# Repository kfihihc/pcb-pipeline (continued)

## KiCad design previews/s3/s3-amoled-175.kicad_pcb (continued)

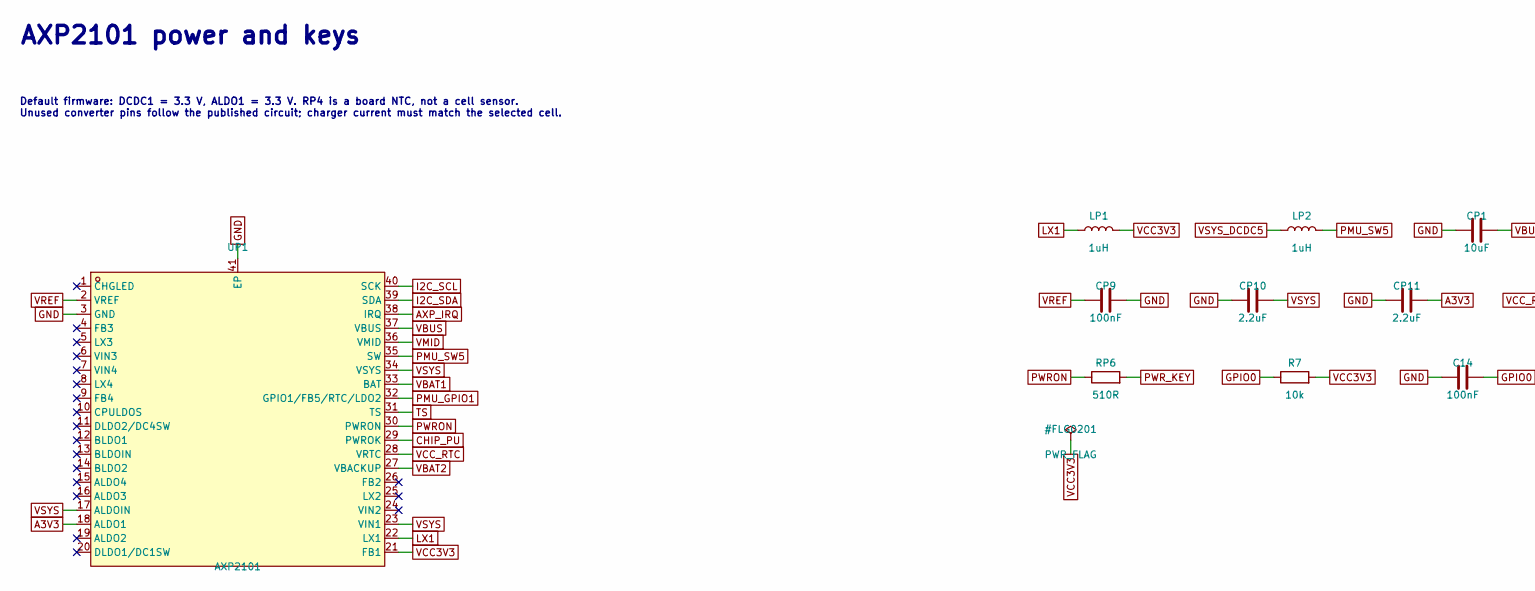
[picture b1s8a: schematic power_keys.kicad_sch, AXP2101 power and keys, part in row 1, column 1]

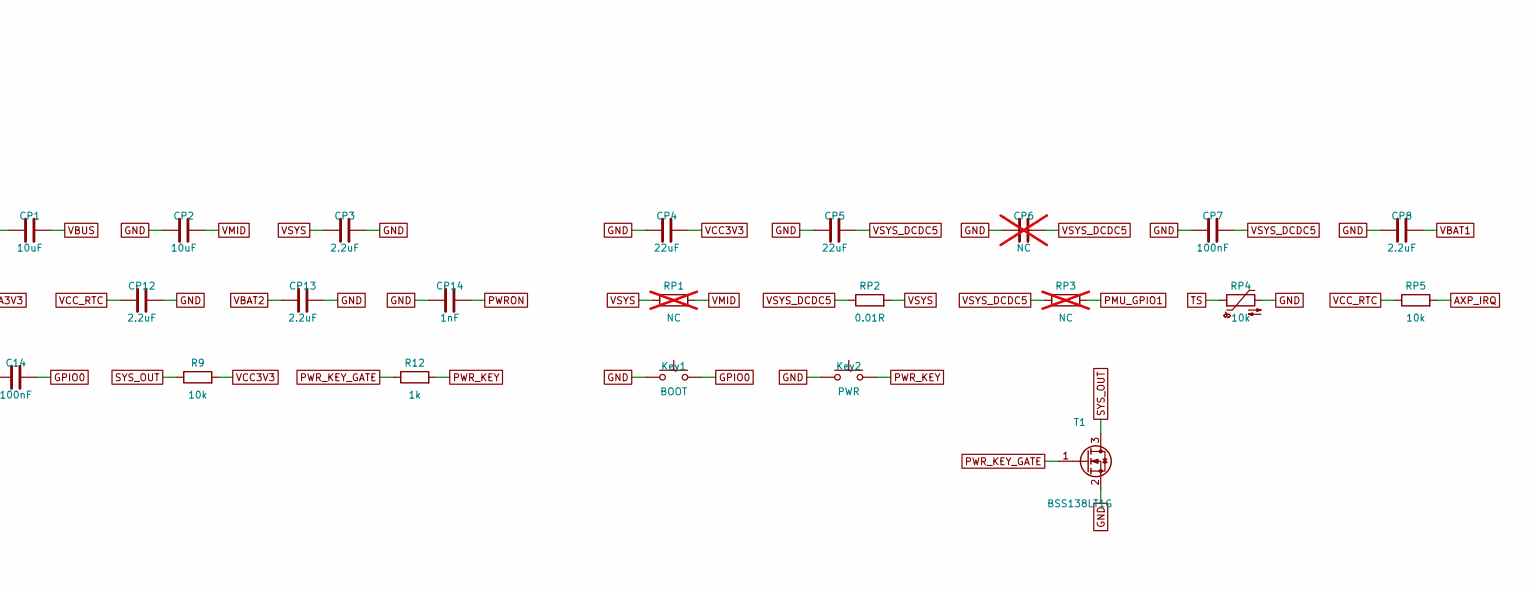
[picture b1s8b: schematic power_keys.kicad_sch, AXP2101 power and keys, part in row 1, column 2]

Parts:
C14: 100nF; C_0201_0603Metric_Tight; LCSC C190183
CP1, CP2: 10uF; C_0603_1608Metric_Tight; LCSC C92487
CP3, CP8, CP10, CP11, CP12, CP13: 2.2uF; C_0201_0603Metric_Tight; LCSC C386031
CP4, CP5: 22uF; C_0603_1608Metric_Tight; LCSC C86295
CP6: NC; C_0201_0603Metric_Tight; not fitted
CP7, CP9: 100nF; C_0201_0603Metric_Tight; LCSC C190183
CP14: 1nF; C_0201_0603Metric_Tight; LCSC C505464
Key1: BOOT; SW_EVPAE_Grounded; MPN EVPAEDB2A; LCSC C79150
Key2: PWR; SW_EVPAE_Grounded; MPN EVPAEDB2A; LCSC C79150
LP1, LP2: 1uH; L_1008_2520Metric_Tight; MPN WPN252012H1R0MT; LCSC C98348
R7, R9: 10k; R_0201_0603Metric_Tight; LCSC C473048
R12: 1k; R_0201_0603Metric_Tight; LCSC C138165
RP1: NC; R_0603_1608Metric_Tight; not fitted
RP2: 0.01R; R_0603_1608Metric_Tight; LCSC C728437
RP3: NC; R_0201_0603Metric_Tight; not fitted
RP4: 10k; R_0603_1608Metric_Tight; MPN NCP18XH103F03RB; LCSC C13564
RP5: 10k; R_0201_0603Metric_Tight; LCSC C473048
RP6: 510R; R_0201_0603Metric_Tight; LCSC C304550
T1: BSS138LT1G; SOT-23; MPN BSS138LT1G; LCSC C82045
UP1: AXP2101; QFN-40_L5.0-W5.0-P0.40-TL-EP3.4; MPN AXP2101; LCSC C3036461

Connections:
A3V3: CP11.2, UP1.18 (ALDO1); also elsewhere on the board
AXP_IRQ: RP5.2, UP1.38 (IRQ)
CHIP_PU: UP1.29 (PWROK); also elsewhere on the board
GND: C14.1, CP1.1, CP2.1, CP3.2, CP4.1, CP5.1, CP6.1, CP7.1, CP8.1, CP9.2, CP10.1, CP11.1, CP12.2, CP13.2, CP14.1, Key1.1, Key2.1, RP4.2, T1.2 (S), UP1.3 (GND), UP1.41 (EP); also elsewhere on the board
GPIO0: C14.2, Key1.2, R7.1; also elsewhere on the board
I2C_SCL: UP1.40 (SCK); also elsewhere on the board
I2C_SDA: UP1.39 (SDA); also elsewhere on the board
LX1: LP1.1, UP1.22 (LX1)
PMU_GPIO1: RP3.2, UP1.32 (GPIO1/FB5/RTC/LDO2)
PMU_SW5: LP2.2, UP1.35 (SW)
PWRON: CP14.2, RP6.1, UP1.30 (PWRON)
PWR_KEY: Key2.2, R12.2, RP6.2
PWR_KEY_GATE: R12.1, T1.1 (G)
SYS_OUT: R9.1, T1.3 (D); also elsewhere on the board
TS: RP4.1, UP1.31 (TS)
VBAT1: CP8.2, UP1.33 (BAT); also elsewhere on the board
VBAT2: CP13.1, UP1.27 (VBACKUP)
VBUS: CP1.2, UP1.37 (VBUS); also elsewhere on the board
VCC3V3: CP4.2, LP1.2, R7.2, R9.2, UP1.21 (FB1); also elsewhere on the board
VCC_RTC: CP12.1, RP5.1, UP1.28 (VRTC)
VMID: CP2.2, RP1.2, UP1.36 (VMID)
VREF: CP9.1, UP1.2 (VREF)
VSYS: CP3.1, CP10.2, RP1.1, RP2.2, UP1.17 (ALDOIN), UP1.23 (VIN1), UP1.34 (VSYS); also elsewhere on the board
VSYS_DCDC5: CP5.2, CP6.2, CP7.2, LP2.1, RP2.1, RP3.1

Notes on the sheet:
Default firmware: DCDC1 = 3.3 V, ALDO1 = 3.3 V. RP4 is a board NTC, not a cell sensor. Unused converter pins follow the published circuit; charger current must match the selected cell.
AXP2101 power and keys

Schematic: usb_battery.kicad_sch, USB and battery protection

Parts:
C108: 100nF; C_0201_0603Metric_Tight; LCSC C190183
H1: USB-C 16P; USB-C-SMD_SHOU_TYPE-C-16P-CB1.6; MPN TYPE-C 16P CB1.6 073; LCSC C2906290
J1: BAT 1.25mm 2P; CONN-SMD_P1.25-H_1.25T-2PWT; MPN 1.25T-2P SMD R/A; LCSC C22074
P1, P2: TP; TestPoint_Pad_D1.0mm_Tight
Q1: AO3400A; SOT-23; MPN AO3400A; LCSC C20917
Q2: AO3401A; SOT-23; MPN AO3401A; LCSC C15127
Q3: MMBT3904; SOT-23; MPN MMBT3904; LCSC C20526
R1, R2: 5.1k; R_0201_0603Metric_Tight; LCSC C473460
R13, R14: 22R; R_0201_0603Metric_Tight; LCSC C155743
R49: 1M; R_0201_0603Metric_Tight; LCSC C295786
R52: 22k; R_0201_0603Metric_Tight; LCSC C473469
R53: 100k; R_0201_0603Metric_Tight; LCSC C106230
TVS1: LTVS16H5.0ET5G; DFN1610-2L_LTVS16H5.0ET5G_Tight; MPN LTVS16H5.0ET5G; LCSC C383280
U9: USBLC6-2P6; SOT-666_Tight; MPN USBLC6-2P6; LCSC C2827693

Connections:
BAT_BASE: Q3.1 (B), R52.2, R53.1
BAT_DETECT: Q2.3 (D), R52.1
BAT_GATE: C108.2, Q1.1 (G), Q3.3 (C), R49.2
BAT_NEG: J1.2, Q1.3 (D), Q2.2 (S)
GND: H1.25 (EH), H1.26 (EH), H1.27 (EH), H1.28 (EH), H1.A1 (GND), H1.A12 (GND), H1.B1 (GND), H1.B12 (GND), J1.3, J1.4, Q1.2 (S), Q3.2 (E), R1.1, R2.1, R53.2, TVS1.2 (A), U9.2 (GND); also elsewhere on the board
USB_CC1: H1.A5 (CC1), R2.2
USB_CC2: H1.B5 (CC2), R1.2
USB_DN_MCU: R13.2; also elsewhere on the board
USB_DP_MCU: R14.2; also elsewhere on the board
USB_N: H1.A7 (DN1), H1.B7 (DN2), P1.1, R13.1, U9.1 (I/O1), U9.6 (I/O1)
USB_P: H1.A6 (DP1), H1.B6 (DP2), P2.1, R14.1, U9.3 (I/O2), U9.4 (I/O2)
VBAT1: C108.1, J1.1, Q2.1 (G), R49.1; also elsewhere on the board
VBUS: H1.A4 (VBUS), H1.A9 (VBUS), H1.B4 (VBUS), H1.B9 (VBUS), TVS1.1 (C), U9.5 (VBUS); also elsewhere on the board

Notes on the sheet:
USB ESD: place U9 at connector. Battery return BAT_NEG must remain isolated from GND. AN171 Fig.4 adapted for 1S; bench validation of hot-plug and charging remains required.
USB and battery protection

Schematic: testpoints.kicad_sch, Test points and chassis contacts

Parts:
H2, H4: MH_GND; MountingHole_1.6mm_PTH_Pad2.35
TP1, TP2, TP3, TP4, TP5, TP6, TP7, TP8, TP9, TP10, TP11, TP12, TP13, TP14, TP15, TP16, TP17, TP18, TP19, TP20, TP21: TP; TestPoint_Pad_D1.0mm_Tight

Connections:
CHIP_PU: TP11.1; also elsewhere on the board
ES7210_DMIC_CLK: TP20.1; also elsewhere on the board
ES7210_INT: TP12.1; also elsewhere on the board
GND: H2.1, H4.1, TP1.1, TP3.1, TP17.1, TP19.1, TP21.1; also elsewhere on the board
GPIO17: TP13.1; also elsewhere on the board
GPIO18: TP14.1; also elsewhere on the board
GPIO39: TP15.1; also elsewhere on the board
GPIO40: TP16.1; also elsewhere on the board
GPIO41: TP9.1; also elsewhere on the board
GPIO42: TP10.1; also elsewhere on the board
I2C_SCL: TP7.1; also elsewhere on the board
I2C_SDA: TP8.1; also elsewhere on the board
U0RXD: TP5.1; also elsewhere on the board
U0TXD: TP6.1; also elsewhere on the board
VBUS: TP2.1; also elsewhere on the board
VCC3V3: TP4.1, TP18.1; also elsewhere on the board

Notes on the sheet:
TP12 = ES7210 INT; TP20 = ES7210 DMIC_CLK. H2/H4: plated 1.6 mm holes, 2.35 mm pad, to GND (PDF edge distance + product photo ring); verify on a unit.
Test points and chassis contacts

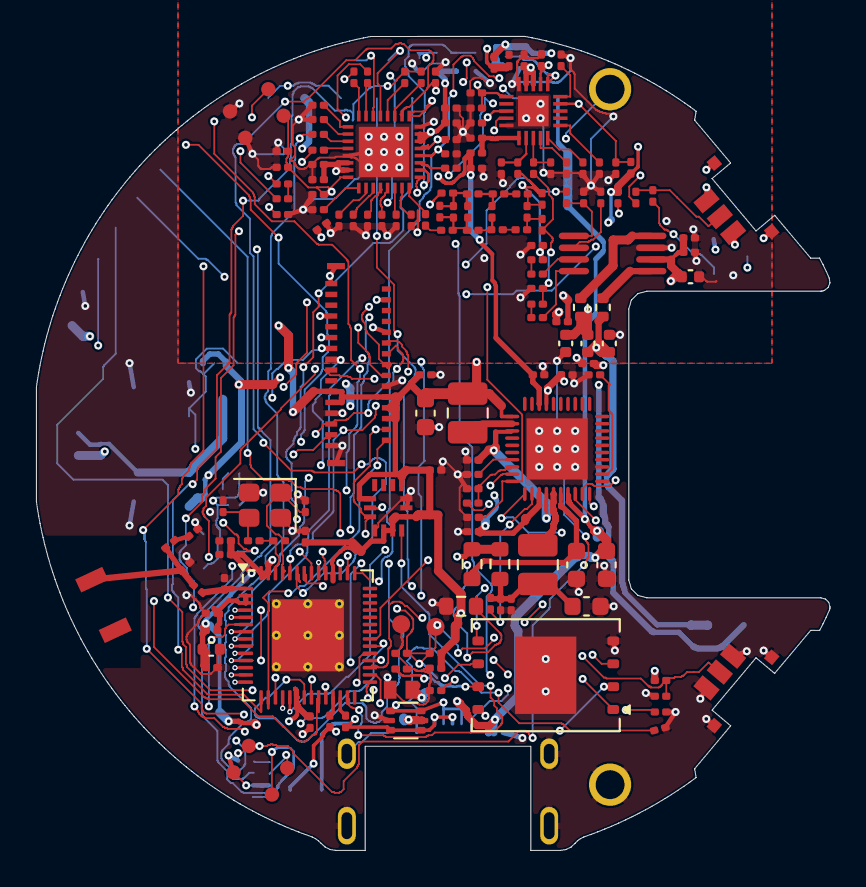
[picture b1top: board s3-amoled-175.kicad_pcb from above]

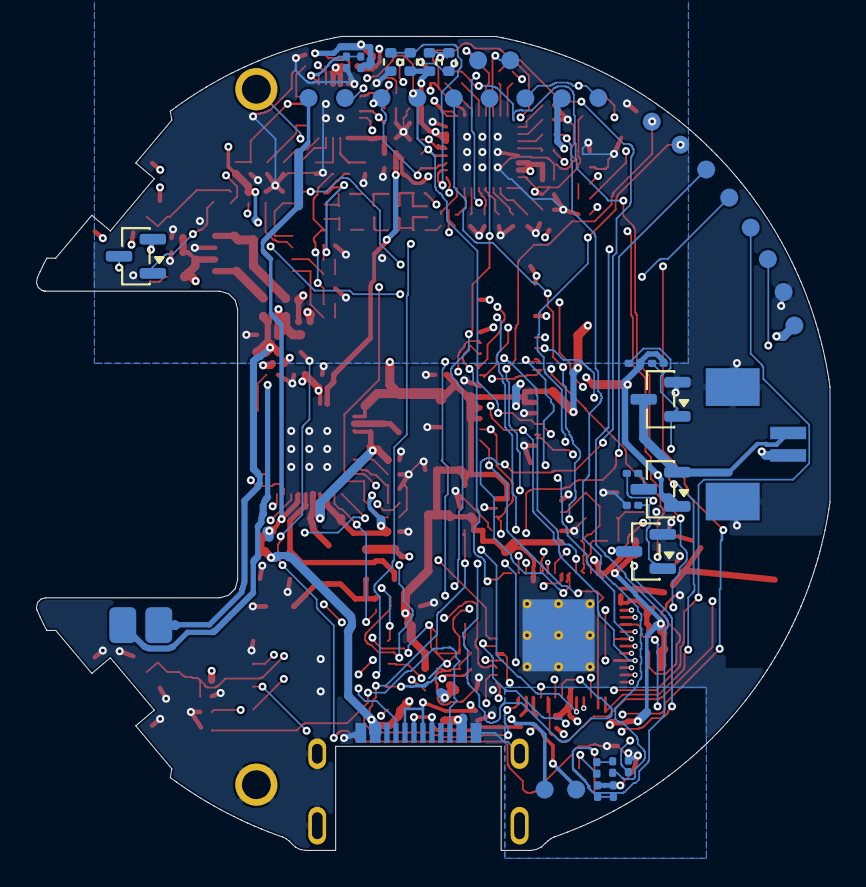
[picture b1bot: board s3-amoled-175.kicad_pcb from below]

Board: 4 copper layers, 44.1 x 45.2 mm, 202 parts (43 on the bottom side), 134 nets.

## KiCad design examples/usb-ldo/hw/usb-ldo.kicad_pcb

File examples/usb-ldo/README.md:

# USB-C 3.3 V LDO demo

> **这是 pcb-pipeline 的端到端示例**：一块 25 × 18 mm 的双层板（USB-C 取电 → HT7533-1 → 3.3 V 和指示灯），2026-10-10 按流程从零做到制造包，全部步骤由脚本完成。它的价值在于流程在各阶段实际拦下的问题，下表逐条列出：
>
> | 阶段 | 发现了什么 | 证据 |
> | --- | --- | --- |
> | 选料 + 仿真 | XC6206 的 VIN 绝对最大值 7.0 V，热插拔峰值 7.6–8.2 V，改用 HT7533-1 | `sim/benches.toml`、D-0002 |
> | 数据手册 | HT7533-1 保证输出只有 70 mA（首页写 100 mA），需求改为 50 mA；立创中文站给的同名 PDF 是另一家厂商的 | `data/parts/HT7533-1/facts.toml` |
> | 数据手册 | LED 原厂引脚编号与 KiCad 相反；USB-C 推荐焊盘是按 1.0 mm 板厚画的 | facts 的 caveat、`docs/reviews/` |
> | 选料 | 每套物料 1.03 美元，超出 0.5 美元目标（连接器占 0.91 美元） | `jlc_parts.py check`、D-0003 |
> | 规则 | 自定义 VBUS 间距规则与 USB-C 焊盘自身的间距冲突 | DRC |
> | 布线 | 自动布线在 USB 外壳下走细线、打盘中孔、无视 `.kicad_dru`；改成禁布区加预布线 | metrics、变更单 0001、D-0005 |
> | 工具 | 摆位原点偏了半个板框线宽（25 µm），修正后用 `layout/rebuild.sh` 重建 | 变更单 0002 |
> | 拼板 | 2×2 试拼时邮票孔落进 USB-C 庭院；连接桥参数写反时板子在拼板里悬空，DRC 却照样干净，改为检查拼板外框只有一块 | D-0006、`layout/panel.toml` |
> | EMC 预检 | kicad-happy 指出 J1 附近没有 ESD 和滤波（IO-001），与 D-0004 的取舍一致，产品化时要加 | `reports/review/emc.md` |
>
> 最终门禁 8 项全过；`release/` 的包标为 REVIEW ONLY，因为它不是从 git 提交生成的。包里另有自拼的 2×1 拼板（`fab/panel/`）、交互式 BOM 和 KiCanvas 页面。

usb-ldo：用 pcb-pipeline 流程管理的 KiCad 10.0.6 工程（pcbkit 0.2.0）。许可：MIT。

| 位置 | 内容 |
| --- | --- |
| `pcb.toml` | 工程清单：文件位置、门禁与 BOM 配置 |
| `docs/` | 需求（SPEC）、设计决定（DECISIONS）、修订记录、审查清单、上电记录、变更单 |
| `parts/parts.csv`、`data/parts/` | 选料登记表；每个器件的数据手册与带页码的事实 |
| `design/` | 设计意图：电路代码（code 模式）与连接意图断言 |
| `hw/` | KiCad 工程：原理图、PCB、自定义规则 `.kicad_dru` |
| `layout/` | 板框、层数、制造下限、网络类、固定摆位；拼板预设 `panel.toml` |
| `checks/metrics.toml`、`sim/` | 项目指标与仿真基准，都进入门禁 |
| `pcbkit/` | 随工程固定版本的工具（门禁、同步、摆位、仿真、审查、发布、可选输出）；用 pcb-pipeline 的 `new_project.py --update-kit` 升级 |

## 常用命令

```bash
uv sync                                   # 可选依赖（SKiDL 等）
uv sync --group extras                    # 可选输出用的 KiKit、InteractiveHtmlBom、PcbDraw（之后单独 uv sync 会把它们去掉）
uv run python design/board.py             # code 模式：由代码生成原理图
python3 pcbkit/board_setup.py             # 按 layout/board.toml 建立或更新板框、层数、规则
python3 pcbkit/sync_pcb.py                # 原理图 -> PCB（封装、网络、字段），不动已有布局
python3 pcbkit/place.py                   # 按 layout/placement.toml 摆放并锁定关键器件
python3 pcbkit/gate.py                    # 合并门禁：ERC、DRC+一致性、规则哨兵、铺铜、连接意图、指标、仿真、复现
python3 pcbkit/board_diff.py old.kicad_pcb hw/usb-ldo.kicad_pcb --scope docs/changes/0001-x.toml
python3 pcbkit/review.py                  # 审查包 reports/review/（另含 KiCanvas、iBOM、PcbDraw 板图、EMC 线索、拼板）
python3 pcbkit/extras.py status           # 可选输出（pcb.toml [outputs]）要哪些、工具装了没有、拼板定了没有
python3 pcbkit/release.py                 # 门禁通过后生成制造与审查包 release/
```

改动流程：分支 → 变更单 `docs/changes/` → 修改 → 门禁 → PR（附报告与版图对比）→ 人工审查合并。详见 pcb-pipeline 技能。

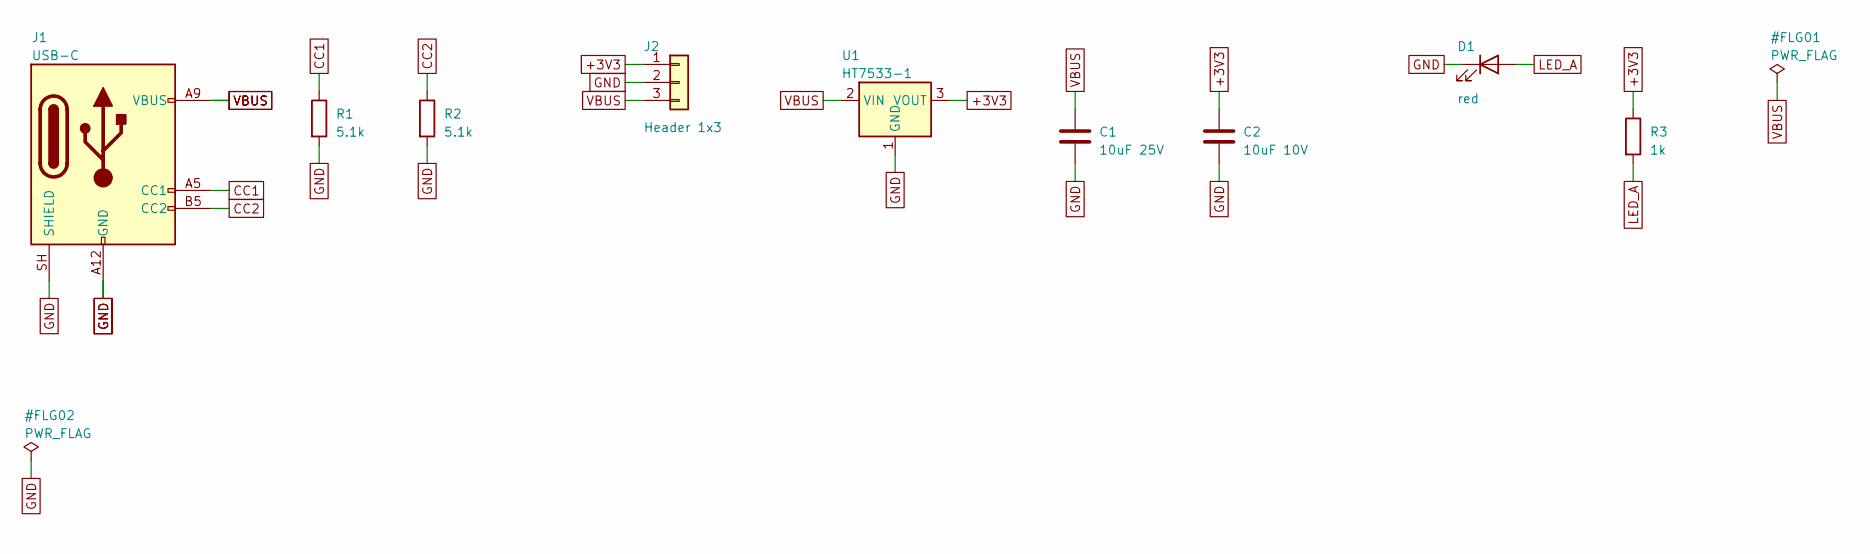
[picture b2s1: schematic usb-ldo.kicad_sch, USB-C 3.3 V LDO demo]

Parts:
C1: 10uF 25V; C_0805_2012Metric; MPN CL21A106KAYNNNE; LCSC C15850
C2: 10uF 10V; C_0603_1608Metric; MPN CL10A106KP8NNNC; LCSC C19702
D1: red; LED_0603_1608Metric; MPN KT-0603R; LCSC C2286
J1: USB-C; USB_C_Receptacle_GCT_USB4125-xx-x-0190_6P_TopMnt_Horizontal; MPN USB4125-GF-A-0190; LCSC C5246813
J2: Header 1x3; PinHeader_1x03_P2.54mm_Vertical; MPN PZ254V-11-03P; LCSC C2937625
R1, R2: 5.1k; R_0603_1608Metric; MPN 0603WAF5101T5E; LCSC C23186
R3: 1k; R_0603_1608Metric; MPN 0603WAF1001T5E; LCSC C21190
U1: HT7533-1; SOT-89-3; MPN HT7533-1; LCSC C14289

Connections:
+3V3: C2.1, J2.1, R3.1, U1.3 (VOUT)
CC1: J1.A5 (CC1), R1.1
CC2: J1.B5 (CC2), R2.1
GND: C1.2, C2.2, D1.1 (K), J1.A12 (GND), J1.B12 (GND), J1.SH (SHIELD), J2.2, R1.2, R2.2, U1.1 (GND)
LED_A: D1.2 (A), R3.2
VBUS: C1.1, J1.A9 (VBUS), J1.B9 (VBUS), J2.3, U1.2 (VIN)

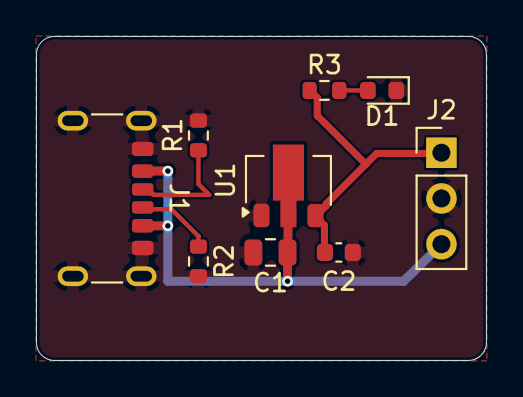
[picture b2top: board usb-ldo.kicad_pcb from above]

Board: 2 copper layers, 25.0 x 18.0 mm, 9 parts (0 on the bottom side), 6 nets.
